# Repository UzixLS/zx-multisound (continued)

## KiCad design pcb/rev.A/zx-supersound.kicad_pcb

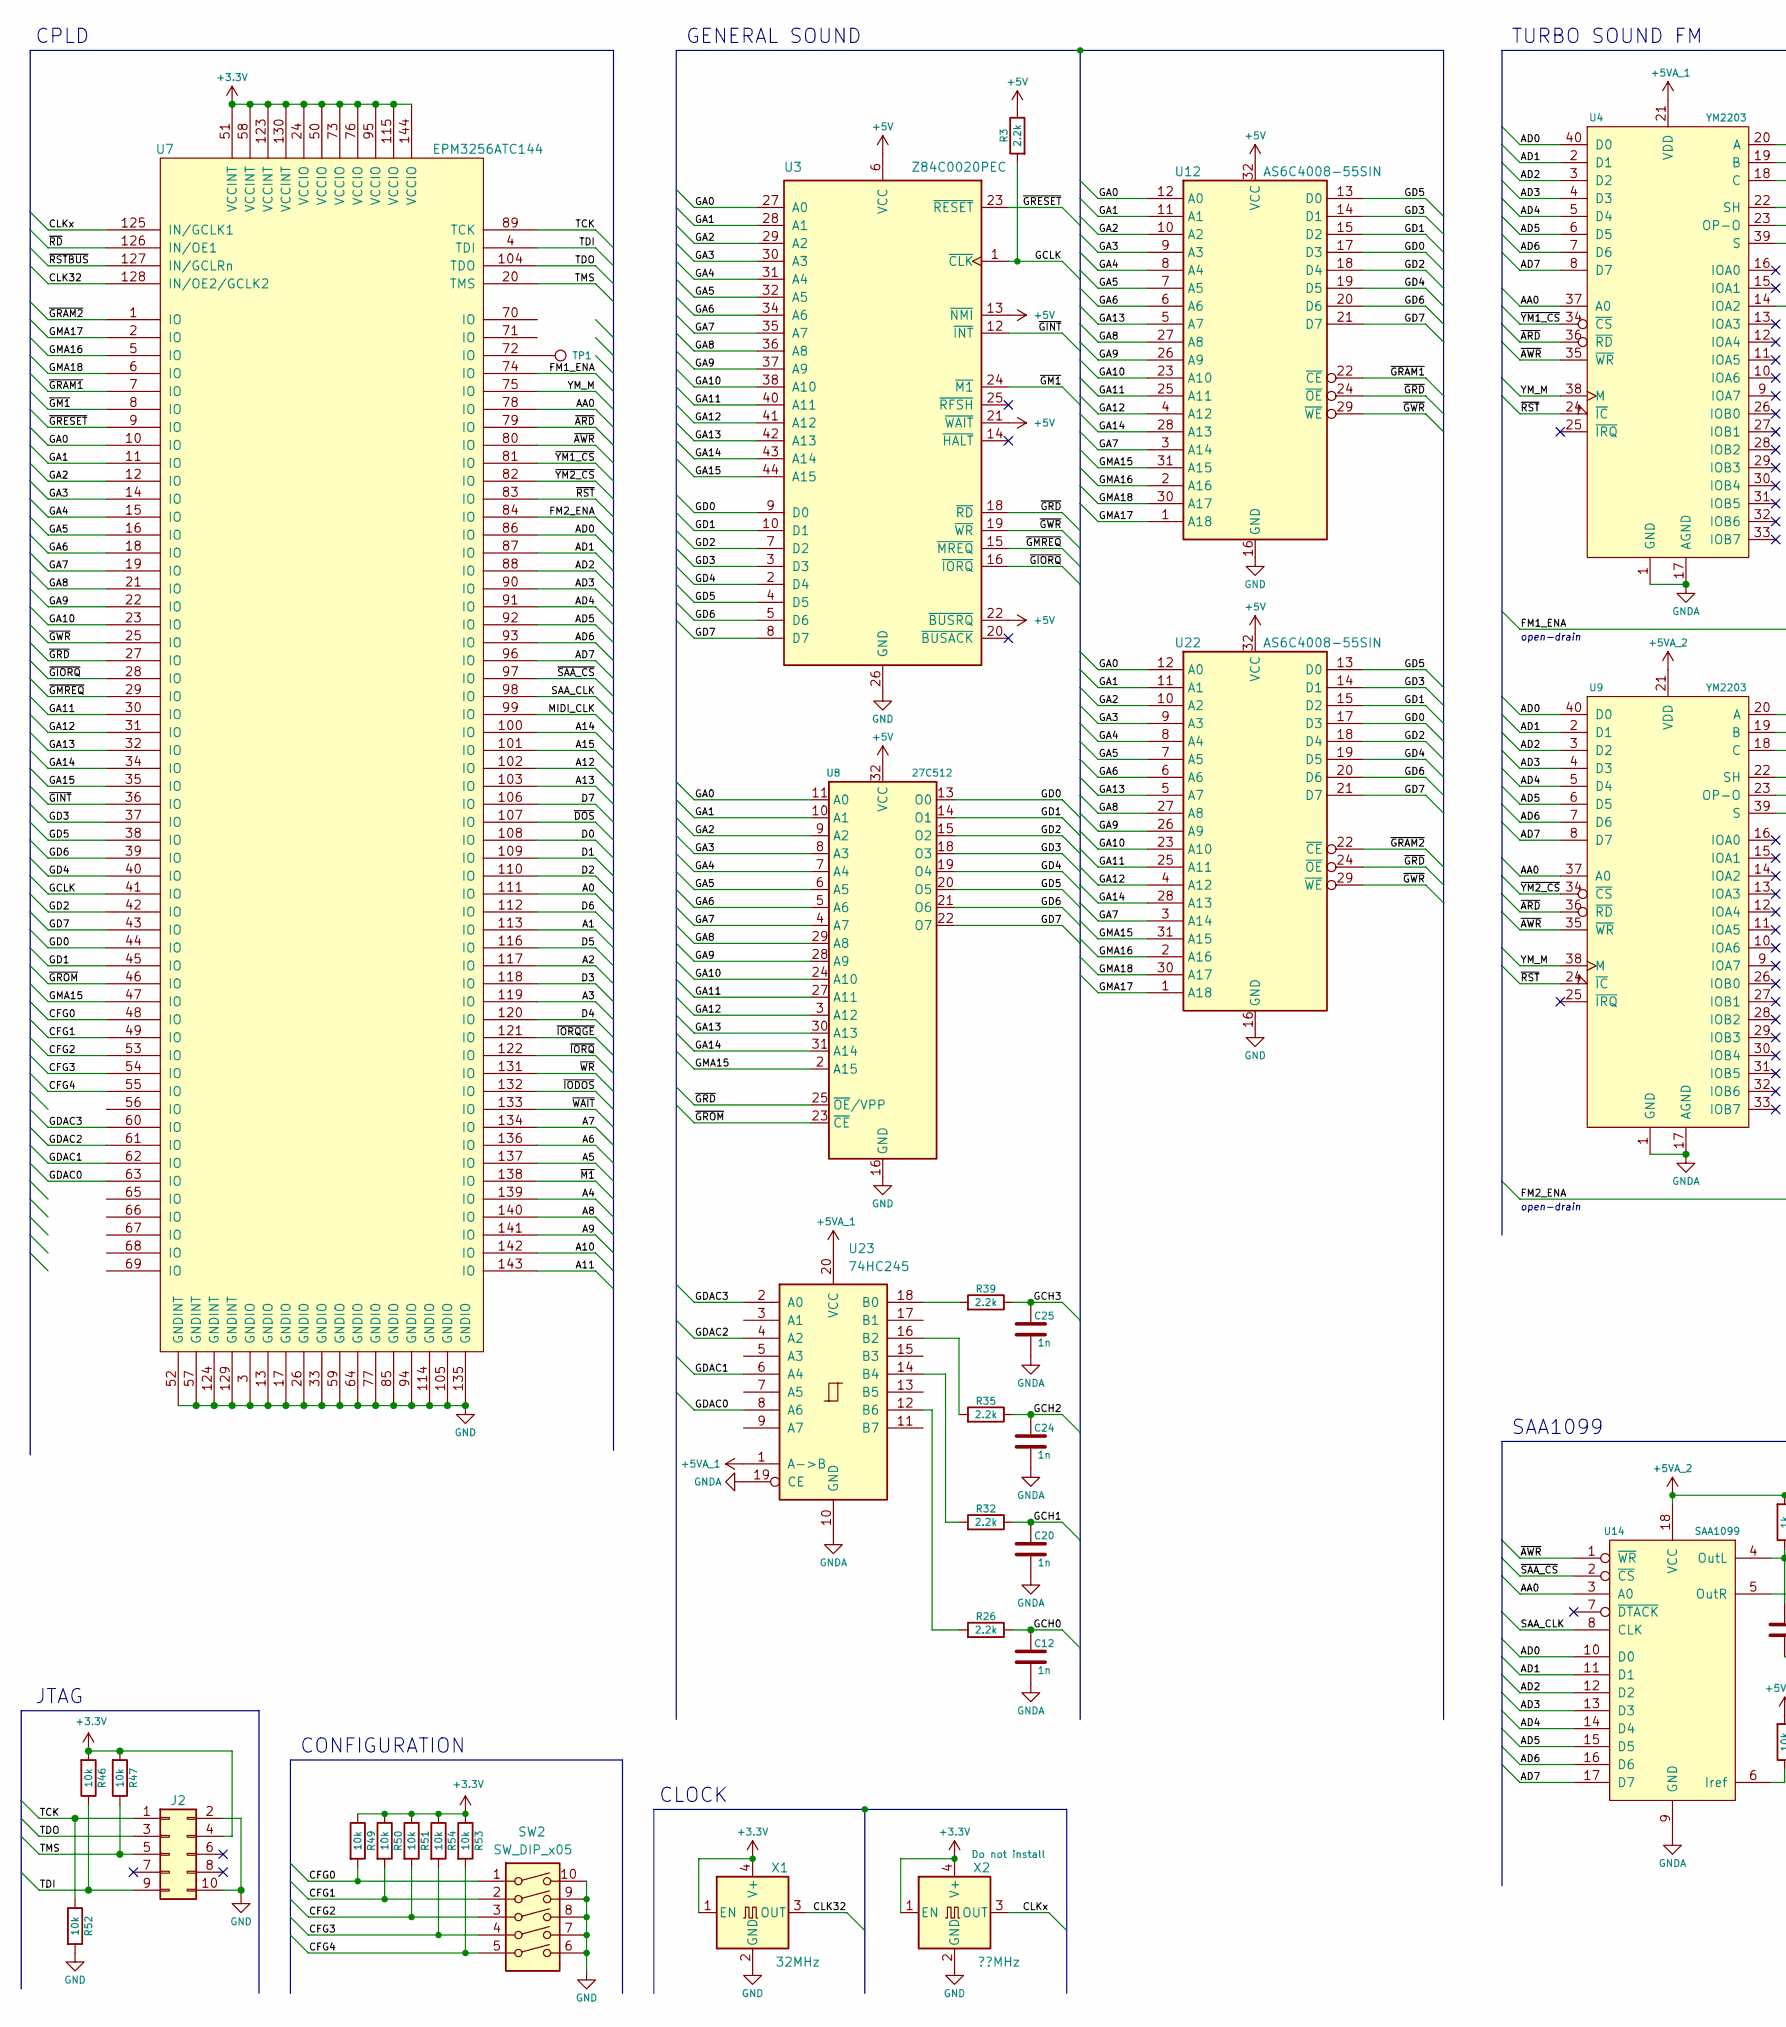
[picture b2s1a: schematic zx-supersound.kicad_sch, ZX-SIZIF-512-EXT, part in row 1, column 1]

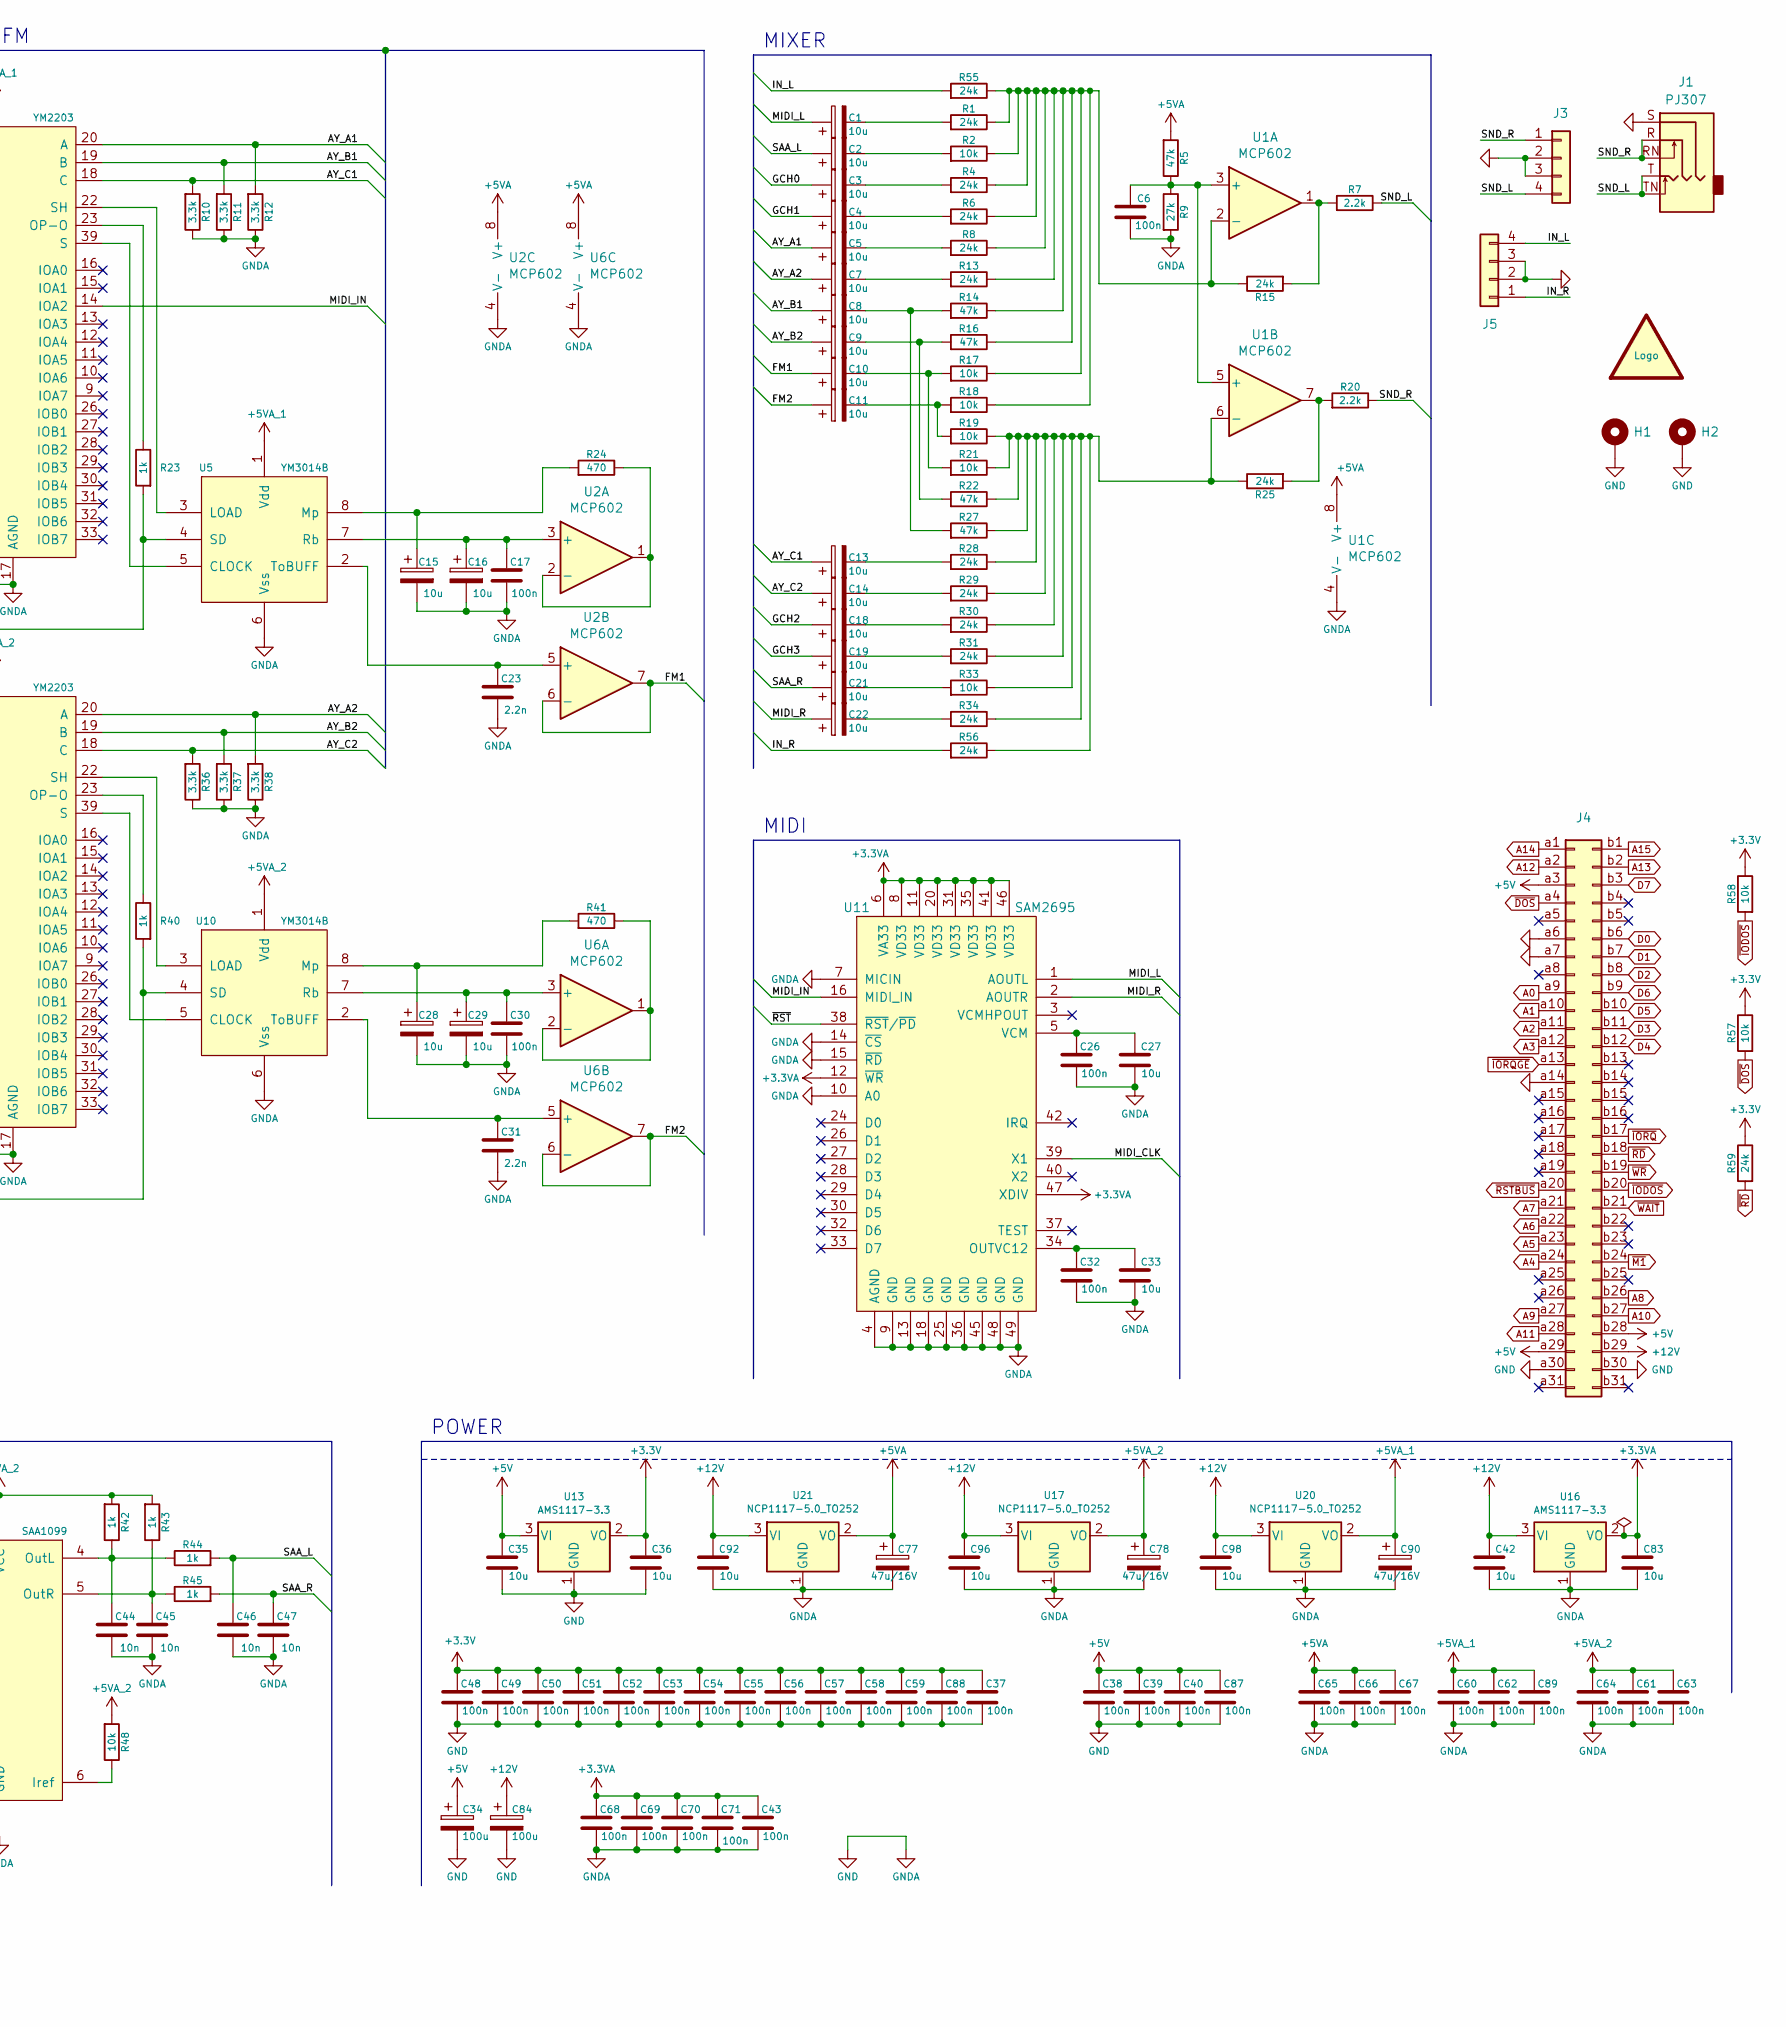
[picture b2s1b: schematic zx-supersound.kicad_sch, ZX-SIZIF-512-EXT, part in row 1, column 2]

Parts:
C1, C2, C3, C4, C5, C7, C8, C9, C10, C11, C13, C14, C15, C16, C18, C19, C21, C22, C28, C29: 10u; CP_Elec_4x5.4
C6, C17, C26, C30, C32, C37, C38, C39, C40, C43, C48, C49, C50, C51, C52, C53, C54, C55, C56, C57, C58, C59, C60, C61, C62, C63, C64, C65, C66, C67, C68, C69, C70, C71, C87, C88, C89: 100n; C_0805_2012Metric_Pad1.18x1.45mm_HandSolder
C12, C20, C24, C25: 1n; C_0805_2012Metric_Pad1.18x1.45mm_HandSolder
C23, C31: 2.2n; C_0805_2012Metric_Pad1.18x1.45mm_HandSolder
C27, C33, C35, C36, C42, C83, C92, C96, C98: 10u; C_1206_3216Metric_Pad1.33x1.80mm_HandSolder
C34, C84: 100u; CP_Elec_6.3x7.7
C44, C45, C46, C47: 10n; C_0805_2012Metric_Pad1.18x1.45mm_HandSolder
C77, C78, C90: 47u/16V; CP_EIA-6032-28_Kemet-C_Pad2.25x2.35mm_HandSolder
H1, H2: MountingHole_Pad; MountingHole_2.7mm_M2.5_DIN965_Pad
J1: PJ307; SWITCHCRAFT_35RAPC4BHN2
J2: PinHeader; PinHeader_2x05_P2.54mm_Vertical
J3, J5: Conn_01x04; PinHeader_1x04_P2.54mm_Vertical
J4: Conn_02x31_Row_Letter_First; ZX_NEMO_EDGE
LOGO1: graphic; black-mage-9.6x6.5
R1, R4, R6, R8, R13, R15, R25, R28, R29, R30, R31, R34, R55, R56, R59: 24k; R_0805_2012Metric_Pad1.20x1.40mm_HandSolder
R2, R17, R18, R19, R21, R33, R46, R47, R48, R49, R50, R51, R52, R53, R54, R57, R58: 10k; R_0805_2012Metric_Pad1.20x1.40mm_HandSolder
R3, R7, R20, R26, R32, R35, R39: 2.2k; R_0805_2012Metric_Pad1.20x1.40mm_HandSolder
R5, R14, R16, R22, R27: 47k; R_0805_2012Metric_Pad1.20x1.40mm_HandSolder
R9: 27k; R_0805_2012Metric_Pad1.20x1.40mm_HandSolder
R10, R11, R12, R36, R37, R38: 3.3k; R_0805_2012Metric_Pad1.20x1.40mm_HandSolder
R23, R40, R42, R43, R44, R45: 1k; R_0805_2012Metric_Pad1.20x1.40mm_HandSolder
R24, R41: 470; R_0805_2012Metric_Pad1.20x1.40mm_HandSolder
SW2: SW_DIP_x05; SW_DIP_SPSTx05_Slide_6.7x14.26mm_W7.62mm_P2.54mm_LowProfile
TP1: TestPoint; TestPoint_Pad_D1.0mm
U1, U2, U6: MCP602; SOIC-8_3.9x4.9mm_P1.27mm
U3: Z84C0020PEC; TQFP-44_14x14mm_P0.8mm
U4, U9: YM2203; DIP-40_W15.24mm_Socket
U5, U10: YM3014B; DIP-8_W7.62mm_Socket
U7: EPM3256ATC144; TQFP-144_20x20mm_P0.5mm
U8: 27C512; PLCC-32_11.4x14.0mm_P1.27mm-longpads
U11: SAM2695; QFN-48-1EP_6x6mm_P0.4mm_EP4.2x4.2mm
U12, U22: AS6C4008-55SIN; SSOP-32_11.305x20.495mm_P1.27mm
U13, U16: AMS1117-3.3; SOT-223-3_TabPin2
U14: SAA1099; DIP-18_W7.62mm_Socket
U17, U20, U21: NCP1117-5.0_TO252; TO-252-2
U23: 74HC245; SOIC-20W_7.5x12.8mm_P1.27mm
X1: 32MHz; Oscillator_SMD_SeikoEpson_SG8002CA-4Pin_7.0x5.0mm
X2: ??MHz; Oscillator_SMD_SeikoEpson_SG8002CA-4Pin_7.0x5.0mm

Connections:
+3.3VA: C43.1, C68.1, C69.1, C70.1, C71.1, C83.1, U11.6 (VA33), U11.8 (VD33), U11.11 (VD33), U11.12 (~WR), U11.20 (VD33), U11.31 (VD33), U11.35 (VD33), U11.41 (VD33), U11.46 (VD33), U11.47 (XDIV), U16.2 (VO)
+3V3: C36.1, C37.2, C48.1, C49.1, C50.1, C51.1, C52.1, C53.1, C54.1, C55.1, C56.1, C57.1, C58.1, C59.1, C88.2, J2.4, R46.2, R47.2, R49.1, R50.1, R51.1, R53.1, R54.1, R57.1, R58.1, R59.1, U7.24 (VCCIO), U7.50 (VCCIO), U7.51 (VCCINT), U7.58 (VCCINT), U7.73 (VCCIO), U7.76 (VCCIO), U7.95 (VCCIO), U7.115 (VCCIO), U7.123 (VCCINT), U7.130 (VCCINT), U7.144 (VCCIO), U13.2 (VO), X1.1 (EN), X1.4 (V+), X2.1 (EN), X2.4 (V+)
+5V: C34.1, C35.1, C38.2, C39.2, C40.2, C87.2, J4.a3, J4.a29, J4.b28, R3.1, U3.6 (VCC), U3.13 (~NMI), U3.21 (~WAIT), U3.22 (~BUSRQ), U8.32 (VCC), U12.32 (VCC), U13.3 (VI), U22.32 (VCC)
+5VA: C65.2, C66.2, C67.2, C77.1, R5.2, U1.8 (V+), U2.8 (V+), U6.8 (V+), U21.2 (VO)
+5VA_1: C60.2, C62.2, C89.2, C90.1, U4.21 (VDD), U5.1 (Vdd), U20.2 (VO), U23.1 (A->B), U23.20 (VCC)
+5VA_2: C61.2, C63.2, C64.2, C78.1, R42.2, R43.2, R48.2, U9.21 (VDD), U10.1 (Vdd), U14.18 (VCC), U17.2 (VO)
+12V: C42.1, C84.1, C92.1, C96.1, C98.1, J4.b29, U16.3 (VI), U17.3 (VI), U20.3 (VI), U21.3 (VI)
/AA0: U4.37 (A0), U7.78 (IO), U9.37 (A0), U14.3 (A0)
/AD0: U4.40 (D0), U7.86 (IO), U9.40 (D0), U14.10 (D0)
/AD1: U4.2 (D1), U7.87 (IO), U9.2 (D1), U14.11 (D1)
/AD2: U4.3 (D2), U7.88 (IO), U9.3 (D2), U14.12 (D2)
/AD3: U4.4 (D3), U7.90 (IO), U9.4 (D3), U14.13 (D3)
/AD4: U4.5 (D4), U7.91 (IO), U9.5 (D4), U14.14 (D4)
/AD5: U4.6 (D5), U7.92 (IO), U9.6 (D5), U14.15 (D5)
/AD6: U4.7 (D6), U7.93 (IO), U9.7 (D6), U14.16 (D6)
/AD7: U4.8 (D7), U7.96 (IO), U9.8 (D7), U14.17 (D7)
/AY_A1: C5.1, R12.2, U4.20 (A)
/AY_A2: C7.1, R38.2, U9.20 (A)
/AY_B1: C8.1, R11.2, U4.19 (B)
/AY_B2: C9.1, R37.2, U9.19 (B)
/AY_C1: C13.1, R10.2, U4.18 (C)
/AY_C2: C14.1, R36.2, U9.18 (C)
/CFG0: R49.2, SW2.1, U7.48 (IO)
/CFG1: R50.2, SW2.2, U7.49 (IO)
/CFG2: R51.2, SW2.3, U7.53 (IO)
/CFG3: R54.2, SW2.4, U7.54 (IO)
/CFG4: R53.2, SW2.5, U7.55 (IO)
/CLK32: U7.128 (IN/OE2/GCLK2), X1.3 (OUT)
/CLKx: U7.125 (IN/GCLK1), X2.3 (OUT)
/FM1: C10.1, U2.6 (-), U2.7
/FM1_ENA: R23.2, U5.4 (SD), U7.74 (IO)
/FM2: C11.1, U6.6 (-), U6.7
/FM2_ENA: R40.2, U7.84 (IO), U10.4 (SD)
/GA0: U3.27 (A0), U7.10 (IO), U8.11 (A0), U12.12 (A0), U22.12 (A0)
/GA1: U3.28 (A1), U7.11 (IO), U8.10 (A1), U12.11 (A1), U22.11 (A1)
/GA2: U3.29 (A2), U7.12 (IO), U8.9 (A2), U12.10 (A2), U22.10 (A2)
/GA3: U3.30 (A3), U7.14 (IO), U8.8 (A3), U12.9 (A3), U22.9 (A3)
/GA4: U3.31 (A4), U7.15 (IO), U8.7 (A4), U12.8 (A4), U22.8 (A4)
/GA5: U3.32 (A5), U7.16 (IO), U8.6 (A5), U12.7 (A5), U22.7 (A5)
/GA6: U3.34 (A6), U7.18 (IO), U8.5 (A6), U12.6 (A6), U22.6 (A6)
/GA7: U3.35 (A7), U7.19 (IO), U8.4 (A7), U12.3 (A14), U22.3 (A14)
/GA8: U3.36 (A8), U7.21 (IO), U8.29 (A8), U12.27 (A8), U22.27 (A8)
/GA9: U3.37 (A9), U7.22 (IO), U8.28 (A9), U12.26 (A9), U22.26 (A9)
/GA10: U3.38 (A10), U7.23 (IO), U8.24 (A10), U12.23 (A10), U22.23 (A10)
/GA11: U3.40 (A11), U7.30 (IO), U8.27 (A11), U12.25 (A11), U22.25 (A11)
/GA12: U3.41 (A12), U7.31 (IO), U8.3 (A12), U12.4 (A12), U22.4 (A12)
/GA13: U3.42 (A13), U7.32 (IO), U8.30 (A13), U12.5 (A7), U22.5 (A7)
/GA14: U3.43 (A14), U7.34 (IO), U8.31 (A14), U12.28 (A13), U22.28 (A13)
/GA15: U3.44 (A15), U7.35 (IO)
/GCH0: C3.1, C12.1, R26.1
/GCH1: C4.1, C20.1, R32.1
/GCH2: C18.1, C24.1, R35.1
/GCH3: C19.1, C25.1, R39.1
/GCLK: R3.2, U3.1 (~CLK), U7.41 (IO)
/GD0: U3.9 (D0), U7.44 (IO), U8.13 (O0), U12.17 (D3), U22.17 (D3)
/GD1: U3.10 (D1), U7.45 (IO), U8.14 (O1), U12.15 (D2), U22.15 (D2)
/GD2: U3.7 (D2), U7.42 (IO), U8.15 (O2), U12.18 (D4), U22.18 (D4)
/GD3: U3.3 (D3), U7.37 (IO), U8.18 (O3), U12.14 (D1), U22.14 (D1)
/GD4: U3.2 (D4), U7.40 (IO), U8.19 (O4), U12.19 (D5), U22.19 (D5)
/GD5: U3.4 (D5), U7.38 (IO), U8.20 (O5), U12.13 (D0), U22.13 (D0)
/GD6: U3.5 (D6), U7.39 (IO), U8.21 (O6), U12.20 (D6), U22.20 (D6)
/GD7: U3.8 (D7), U7.43 (IO), U8.22 (O7), U12.21 (D7), U22.21 (D7)
/GDAC0: U7.63 (IO), U23.8 (A6)
/GDAC1: U7.62 (IO), U23.6 (A4)
/GDAC2: U7.61 (IO), U23.4 (A2)
/GDAC3: U7.60 (IO), U23.2 (A0)
/GMA15: U7.47 (IO), U8.2 (A15), U12.31 (A15), U22.31 (A15)
/GMA16: U7.5 (IO), U12.2 (A16), U22.2 (A16)
/GMA17: U7.2 (IO), U12.1 (A18), U22.1 (A18)
/GMA18: U7.6 (IO), U12.30 (A17), U22.30 (A17)
/IN_L: J5.4, R55.2
/IN_R: J5.1, R56.2
/MIDI_CLK: U7.99 (IO), U11.39 (X1)
/MIDI_IN: U4.14 (IOA2), U11.16 (MIDI_IN)
/MIDI_L: C1.1, U11.1 (AOUTL)
/MIDI_R: C22.1, U11.2 (AOUTR)
/SAA_CLK: U7.98 (IO), U14.8 (CLK)
/SAA_L: C2.1, C46.1, R44.2
/SAA_R: C21.1, C47.1, R45.2
/SND_L: J1.T, J1.TN, J3.4, R7.1
/SND_R: J1.R, J1.RN, J3.1, R20.1
/TCK: J2.1, R52.1, U7.89 (TCK)
/TDI: J2.9, R46.1, U7.4 (TDI)
/TDO: J2.3, U7.104 (TDO)
/TMS: J2.5, R47.1, U7.20 (TMS)
/YM_M: U4.38 (M), U7.75 (IO), U9.38 (M)
/~ARD: U4.36 (~RD), U7.79 (IO), U9.36 (~RD)
/~AWR: U4.35 (~WR), U7.80 (IO), U9.35 (~WR), U14.1 (~WR)
/~GINT: U3.12 (~INT), U7.36 (IO)
/~GIORQ: U3.16 (~IORQ), U7.28 (IO)
/~GM1: U3.24 (~M1), U7.8 (IO)
/~GMREQ: U3.15 (~MREQ), U7.29 (IO)
/~GRAM1: U7.7 (IO), U12.22 (~CE)
/~GRAM2: U7.1 (IO), U22.22 (~CE)
/~GRD: U3.18 (~RD), U7.27 (IO), U8.25 (~OE/VPP), U12.24 (~OE), U22.24 (~OE)
/~GRESET: U3.23 (~RESET), U7.9 (IO)
/~GROM: U7.46 (IO), U8.23 (~CE)
/~GWR: U3.19 (~WR), U7.25 (IO), U12.29 (~WE), U22.29 (~WE)
/~RST: U4.24 (~IC), U7.83 (IO), U9.24 (~IC), U11.38 (~RST/~PD)
/~SAA_CS: U7.97 (IO), U14.2 (~CS)
/~YM1_CS: U4.34 (~CS), U7.81 (IO)
/~YM2_CS: U7.82 (IO), U9.34 (~CS)
A0: J4.a9, U7.111 (IO)
A1: J4.a10, U7.113 (IO)
A2: J4.a11, U7.117 (IO)
A3: J4.a12, U7.119 (IO)
A4: J4.a24, U7.139 (IO)
A5: J4.a23, U7.137 (IO)
A6: J4.a22, U7.136 (IO)
A7: J4.a21, U7.134 (IO)
A8: J4.b26, U7.140 (IO)
A9: J4.a27, U7.141 (IO)
A10: J4.b27, U7.142 (IO)
A11: J4.a28, U7.143 (IO)
A12: J4.a2, U7.102 (IO)
A13: J4.b2, U7.103 (IO)
A14: J4.a1, U7.100 (IO)
A15: J4.b1, U7.101 (IO)
D0: J4.b6, U7.108 (IO)
D1: J4.b7, U7.109 (IO)
D2: J4.b8, U7.110 (IO)
D3: J4.b11, U7.118 (IO)
D4: J4.b12, U7.120 (IO)
D5: J4.b10, U7.116 (IO)
D6: J4.b9, U7.112 (IO)
D7: J4.b3, U7.106 (IO)
GND: C6.1, C12.2, C15.2, C16.2, C17.2, C20.2, C23.2, C24.2, C25.2, C26.2, C27.2, C28.2, C29.2, C30.2, C31.2, C32.2, C33.2, C34.2, C35.2, C36.2, C37.1, C38.1, C39.1, C40.1, C42.2, C43.2, C44.2, C45.2, C46.2, C47.2, C48.2, C49.2, C50.2, C51.2, C52.2, C53.2, C54.2, C55.2, C56.2, C57.2, C58.2, C59.2, C60.1, C61.1, C62.1, C63.1, C64.1, C65.1, C66.1, C67.1, C68.2, C69.2, C70.2, C71.2, C77.2, C78.2, C83.2, C84.2, C87.1, C88.1, C89.1, C90.2, C92.2, C96.2, C98.2, H1.1, H2.1, J1.S, J2.2, J2.10, J3.2, J3.3, J4.a6, J4.a7, J4.a14, J4.a30, J4.b30, J5.2, J5.3, R9.2, R10.1, R11.1, R12.1, R36.1, R37.1, R38.1, R52.2, SW2.6, SW2.7, SW2.8, SW2.9, SW2.10, U1.4 (V-), U2.4 (V-), U3.26 (GND), U4.1 (GND), U4.17 (AGND), U5.6 (Vss), U6.4 (V-), U7.3 (GNDIO), U7.13 (GNDIO), U7.17 (GNDIO), U7.26 (GNDIO), U7.33 (GNDIO), U7.52 (GNDINT), U7.57 (GNDINT), U7.59 (GNDIO), U7.64 (GNDIO), U7.77 (GNDIO), U7.85 (GNDIO), U7.94 (GNDIO), U7.105 (GNDIO), U7.114 (GNDIO), U7.124 (GNDINT), U7.129 (GNDINT), U7.135 (GNDIO), U8.16 (GND), U9.1 (GND), U9.17 (AGND), U10.6 (Vss), U11.4 (AGND), U11.7 (MICIN), U11.9 (GND), U11.10 (A0), U11.13 (GND), U11.14 (~CS), U11.15 (~RD), U11.18 (GND), U11.25 (GND), U11.36 (GND), U11.45 (GND), U11.48 (GND), U11.49 (GND), U12.16 (GND), U13.1 (GND), U14.9 (GND), U16.1 (GND), U17.1 (GND), U20.1 (GND), U21.1 (GND), U22.16 (GND), U23.10 (GND), U23.19 (CE), X1.2 (GND), X2.2 (GND)
unnamed: C1.2, R1.2
unnamed: C2.2, R2.2
unnamed: C3.2, R4.2
unnamed: C4.2, R6.2
unnamed: C5.2, R8.2
unnamed: C6.2, R5.1, R9.1, U1.3 (+), U1.5 (+)
unnamed: C7.2, R13.2
unnamed: C8.2, R14.2, R27.2
unnamed: C9.2, R16.2, R22.2
unnamed: C10.2, R17.2, R21.2
unnamed: C11.2, R18.2, R19.2
unnamed: C13.2, R28.2
unnamed: C14.2, R29.2
unnamed: C15.1, R24.2, U5.8 (Mp)
unnamed: C16.1, C17.1, U2.3 (+), U5.7 (Rb)
unnamed: C18.2, R30.2
unnamed: C19.2, R31.2
unnamed: C21.2, R33.2
unnamed: C22.2, R34.2
unnamed: C23.1, U2.5 (+), U5.2 (ToBUFF)
unnamed: C26.1, C27.1, U11.5 (VCM)
unnamed: C28.1, R41.2, U10.8 (Mp)
unnamed: C29.1, C30.1, U6.3 (+), U10.7 (Rb)
unnamed: C31.1, U6.5 (+), U10.2 (ToBUFF)
unnamed: C32.1, C33.1, U11.34 (OUTVC12)
unnamed: C44.1, R42.1, R44.1, U14.4 (OutL)
unnamed: C45.1, R43.1, R45.1, U14.5 (OutR)
unnamed: R1.1, R2.1, R4.1, R6.1, R8.1, R13.1, R14.1, R15.1, R16.1, R17.1, R18.1, R55.1, U1.2 (-)
unnamed: R7.2, R15.2, U1.1
unnamed: R19.1, R21.1, R22.1, R25.1, R27.1, R28.1, R29.1, R30.1, R31.1, R33.1, R34.1, R56.1, U1.6 (-)
unnamed: R20.2, R25.2, U1.7
unnamed: R23.1, U4.23 (OP-O)
unnamed: R24.1, U2.1, U2.2 (-)
unnamed: R26.2, U23.12 (B6)
unnamed: R32.2, U23.14 (B4)
unnamed: R35.2, U23.16 (B2)
unnamed: R39.2, U23.18 (B0)
unnamed: R40.1, U9.23 (OP-O)
unnamed: R41.1, U6.1, U6.2 (-)
unnamed: R48.1, U14.6 (Iref)
unnamed: TP1.1, U7.72 (IO)
unnamed: U4.22 (SH), U5.3 (LOAD)
unnamed: U4.39 (S), U5.5 (CLOCK)
unnamed: U9.22 (SH), U10.3 (LOAD)
unnamed: U9.39 (S), U10.5 (CLOCK)
~DOS: J4.a4, R57.2, U7.107 (IO)
~IODOS: J4.b20, R58.2, U7.132 (IO)
~IORQGE: J4.a13, U7.121 (IO)
~IORQ: J4.b17, U7.122 (IO)
~M1: J4.b24, U7.138 (IO)
~RD: J4.b18, R59.2, U7.126 (IN/OE1)
~RSTBUS: J4.a20, U7.127 (IN/GCLRn)
~WAIT: J4.b21, U7.133 (IO)
~WR: J4.b19, U7.131 (IO)

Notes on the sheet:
SAA1099
CONFIGURATION
open-drain
GENERAL SOUND
TURBO SOUND FM
MIXER
CPLD
JTAG
POWER
MIDI
CLOCK

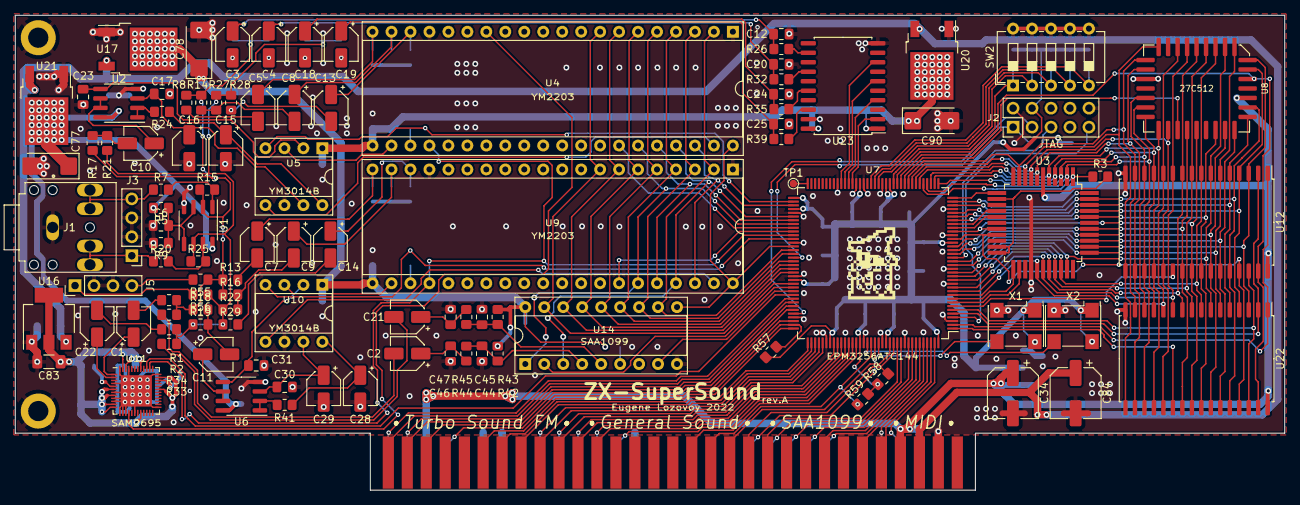
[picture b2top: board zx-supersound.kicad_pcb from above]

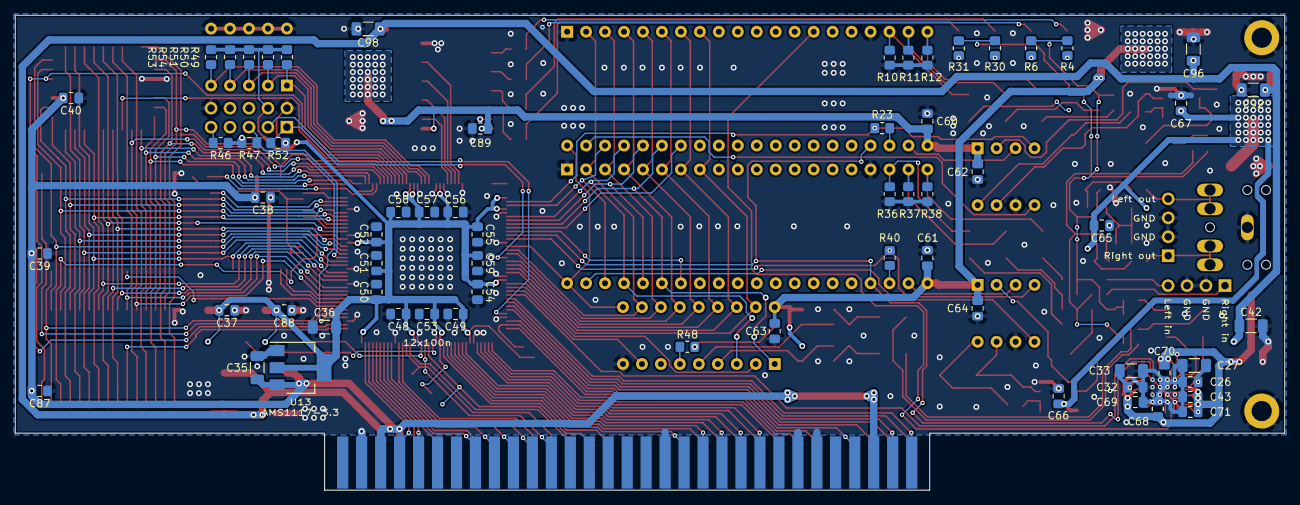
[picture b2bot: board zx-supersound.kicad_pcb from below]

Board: 2 copper layers, 170.0 x 63.6 mm, 172 parts (64 on the bottom side), 181 nets.

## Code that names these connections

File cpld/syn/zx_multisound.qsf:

# -------------------------------------------------------------------------- #
#
# Copyright (C) 1991-2013 Altera Corporation
# Your use of Altera Corporation's design tools, logic functions 
# and other software and tools, and its AMPP partner logic 
# functions, and any output files from any of the foregoing 
# (including device programming or simulation files), and any 
# associated documentation or information are expressly subject 
# to the terms and conditions of the Altera Program License 
# Subscription Agreement, Altera MegaCore Function License 
# Agreement, or other applicable license agreement, including, 
# without limitation, that your use is for the sole purpose of 
# programming logic devices manufactured by Altera and sold by 
# Altera or its authorized distributors.  Please refer to the 
# applicable agreement for further details.
#
# -------------------------------------------------------------------------- #
#
# Quartus II 64-Bit
# Version 13.0.1 Build 232 06/12/2013 Service Pack 1 SJ Full Version
# Date created = 12:04:27  October 04, 2020
#
# -------------------------------------------------------------------------- #
#
# Notes:
#
# 1) The default values for assignments are stored in the file:
#		zx_multisound_assignment_defaults.qdf
#    If this file doesn't exist, see file:
#		assignment_defaults.qdf
#
# 2) Altera recommends that you do not modify this file. This
#    file is updated automatically by the Quartus II software
#    and any changes you make may be lost or overwritten.
#
# -------------------------------------------------------------------------- #


set_global_assignment -name FAMILY MAX3000A
set_global_assignment -name DEVICE "EPM3256ATC144-10"
set_global_assignment -name TOP_LEVEL_ENTITY zx_multisound
set_global_assignment -name ORIGINAL_QUARTUS_VERSION "13.0 SP1"
set_global_assignment -name PROJECT_CREATION_TIME_DATE "12:04:27  OCTOBER 04, 2020"
set_global_assignment -name LAST_QUARTUS_VERSION "13.0 SP1"
set_global_assignment -name PROJECT_OUTPUT_DIRECTORY output
set_global_assignment -name DEVICE_FILTER_PIN_COUNT 144
set_global_assignment -name ERROR_CHECK_FREQUENCY_DIVISOR "-1"
set_global_assignment -name MIN_CORE_JUNCTION_TEMP 0
set_global_assignment -name MAX_CORE_JUNCTION_TEMP 85
set_global_assignment -name SDC_FILE clocks.sdc
set_global_assignment -name VERILOG_FILE ../rtl/top.v
set_global_assignment -name VHDL_INPUT_VERSION VHDL_2008
set_global_assignment -name VHDL_SHOW_LMF_MAPPING_MESSAGES OFF
set_global_assignment -name VERILOG_INPUT_VERSION SYSTEMVERILOG_2005
set_global_assignment -name VERILOG_SHOW_LMF_MAPPING_MESSAGES OFF
set_global_assignment -name MAX7000_DEVICE_IO_STANDARD "3.3-V LVTTL"
set_global_assignment -name SAVE_DISK_SPACE OFF
set_global_assignment -name TIMEQUEST_MULTICORNER_ANALYSIS OFF
set_global_assignment -name SYNTH_TIMING_DRIVEN_SYNTHESIS OFF
set_location_assignment PIN_2 -to d[2]
set_location_assignment PIN_7 -to ad[1]
set_location_assignment PIN_8 -to ad[2]
set_location_assignment PIN_9 -to ad[3]
set_location_assignment PIN_10 -to ad[4]
set_location_assignment PIN_11 -to ad[5]
set_location_assignment PIN_12 -to ad[6]
set_location_assignment PIN_14 -to ad[7]
set_location_assignment PIN_15 -to n_saa_cs
set_location_assignment PIN_16 -to saa_clk
set_location_assignment PIN_19 -to n_ym2_cs
set_location_assignment PIN_18 -to n_ym1_cs
set_location_assignment PIN_21 -to n_awr
set_location_assignment PIN_22 -to n_ard
set_location_assignment PIN_23 -to aa0
set_location_assignment PIN_25 -to ym_m
set_location_assignment PIN_27 -to ad[0]
set_location_assignment PIN_28 -to fm2_ena
set_location_assignment PIN_29 -to fm1_ena
set_location_assignment PIN_35 -to midi_clk
set_location_assignment PIN_36 -to gdac3
set_location_assignment PIN_37 -to gdac2
set_location_assignment PIN_38 -to gdac1
set_location_assignment PIN_39 -to gdac0
set_location_assignment PIN_40 -to ga[11]
set_location_assignment PIN_41 -to gclk
set_location_assignment PIN_67 -to ga[1]
set_location_assignment PIN_42 -to ga[12]
set_location_assignment PIN_43 -to ga[13]
set_location_assignment PIN_44 -to ga[14]
set_location_assignment PIN_45 -to ga[15]
set_location_assignment PIN_46 -to ga[10]
set_location_assignment PIN_47 -to ga[9]
set_location_assignment PIN_48 -to ga[8]
set_location_assignment PIN_49 -to n_gint
set_location_assignment PIN_53 -to ga[7]
set_location_assignment PIN_54 -to n_gmreq
set_location_assignment PIN_55 -to ga[6]
set_location_assignment PIN_56 -to n_giorq
set_location_assignment PIN_60 -to ga[5]
set_location_assignment PIN_61 -to n_grst
set_location_assignment PIN_62 -to ga[4]
set_location_assignment PIN_63 -to n_gm1
set_location_assignment PIN_65 -to ga[3]
set_location_assignment PIN_66 -to ga[2]
set_location_assignment PIN_68 -to ga[0]
set_location_assignment PIN_69 -to gma[16]
set_location_assignment PIN_70 -to gma[17]
set_location_assignment PIN_71 -to gd[0]
set_location_assignment PIN_72 -to gd[7]
set_location_assignment PIN_74 -to gd[6]
set_location_assignment PIN_75 -to gd[1]
set_location_assignment PIN_78 -to gd[5]
set_location_assignment PIN_79 -to gd[2]
set_location_assignment PIN_80 -to gd[3]
set_location_assignment PIN_81 -to gd[4]
set_location_assignment PIN_82 -to n_grd
set_location_assignment PIN_83 -to n_gram
set_location_assignment PIN_84 -to n_gwr
set_location_assignment PIN_86 -to gma[18]
set_location_assignment PIN_87 -to gma[15]
set_location_assignment PIN_88 -to n_grom
set_location_assignment PIN_90 -to cfg[0]
set_location_assignment PIN_91 -to cfg[1]
set_location_assignment PIN_92 -to cfg[2]
set_location_assignment PIN_98 -to a[8]
set_location_assignment PIN_99 -to n_wait
set_location_assignment PIN_100 -to a[12]
set_location_assignment PIN_101 -to a[9]
set_location_assignment PIN_102 -to a[11]
set_location_assignment PIN_103 -to a[10]
set_location_assignment PIN_107 -to n_iorq
set_location_assignment PIN_108 -to d[7]
set_location_assignment PIN_109 -to n_wr
set_location_assignment PIN_110 -to d[6]
set_location_assignment PIN_111 -to n_rd
set_location_assignment PIN_112 -to d[5]
set_location_assignment PIN_113 -to n_iorqge
set_location_assignment PIN_116 -to a[13]
set_location_assignment PIN_117 -to d[4]
set_location_assignment PIN_118 -to d[3]
set_location_assignment PIN_119 -to a[15]
set_location_assignment PIN_120 -to a[14]
set_location_assignment PIN_121 -to n_m1
set_location_assignment PIN_132 -to a[7]
set_location_assignment PIN_133 -to a[6]
set_location_assignment PIN_134 -to a[4]
set_location_assignment PIN_136 -to a[3]
set_location_assignment PIN_137 -to a[2]
set_location_assignment PIN_138 -to a[1]
set_location_assignment PIN_139 -to a[0]
set_location_assignment PIN_140 -to a[5]
set_location_assignment PIN_141 -to d[0]
set_location_assignment PIN_142 -to d[1]
set_location_assignment PIN_128 -to clk32
set_location_assignment PIN_127 -to rst_n
set_global_assignment -name MAX7000_OPTIMIZATION_TECHNIQUE BALANCED
set_global_assignment -name SYNTHESIS_SEED 1
set_global_assignment -name ALLOW_POWER_UP_DONT_CARE OFF
set_global_assignment -name PRE_MAPPING_RESYNTHESIS OFF
set_location_assignment PIN_125 -to clkx

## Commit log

2022-06-02 init
2022-06-02 wip pcb rev.A
2022-06-11 add cpld sources
2022-10-29 update gitignore
2022-11-10 update pcb rev.A - final version; add errata
2022-11-15 update cpld firmware - finally working version
2022-11-18 add gs rom
2022-11-18 add testbench
2022-11-18 add pcb rev.A1
2022-11-19 add license
2022-11-19 add readme
2022-11-25 general sound - 16mhz clock
2022-12-18 refactor gs register names
2022-12-18 fix gs glitches with contended timings
2023-02-03 cpld: add build option to support 2mb gs ram
2023-03-26 fix compatibility with NemoIDE
2023-08-19 gs refactor
2023-12-24 exclude ports #0F, #1F, #4F, #5F from iorqge signal
2023-12-24 exclude port #FF from iorqge signal
2024-01-25 swap YM chips (fixes stellar.scl)
2024-04-03 add 2mb pof file variant
2024-10-02 add quartus 2mb project revision (forgot to add within d11ef18c)
2025-01-28 update pcb rev.A and rev.A1 errata
2025-03-29 rename "out" -> "release"; merge 3d view into pdf
2025-03-29 add pcb rev.A2
2025-08-18 cpld: refactor signal names for better readability
2026-06-17 remove raw=true from README links
